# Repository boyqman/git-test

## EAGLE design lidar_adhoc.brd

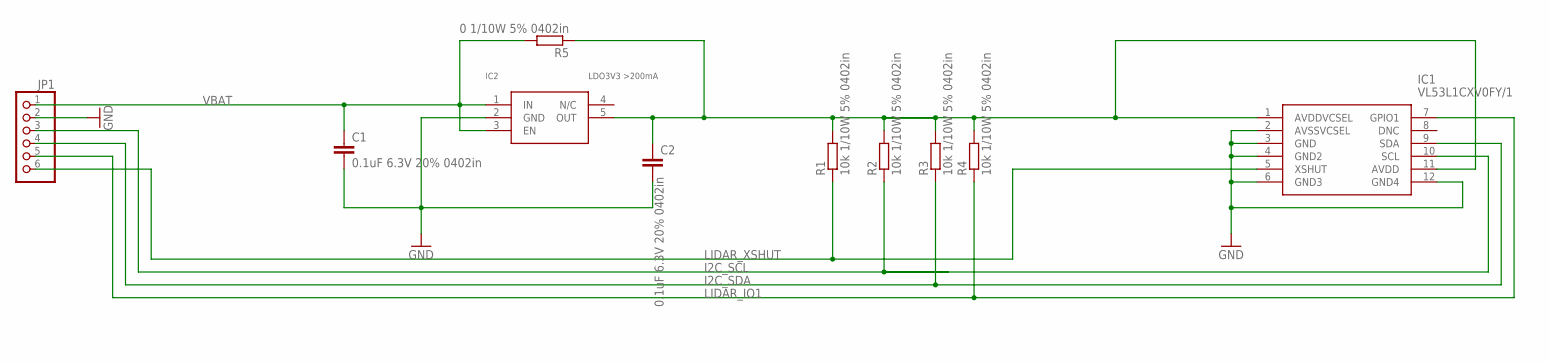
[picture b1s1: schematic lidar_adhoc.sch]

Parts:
C1, C2: 0.1uF 6.3V 20% 0402in; C0402K
IC1: VL53L1CXV0FY/1; VL53L1CXV0FY1
IC2: LDO3V3 >200mA; LDO3V3
JP1: PINHD-1X6; 1X06
R1, R2, R3, R4: 10k 1/10W 5% 0402in; C0402K
R5: 0 1/10W 5% 0402in; C0402K

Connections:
3V3_LIDAR1: C2.1, IC1.1 (AVDDVCSEL), IC1.11 (AVDD), IC2.5 (OUT), R1.2, R2.2, R3.2, R4.2, R5.1
GND: C1.2, C2.2, IC1.2 (AVSSVCSEL), IC1.3 (GND), IC1.4 (GND2), IC1.6 (GND3), IC1.12 (GND4), IC2.2 (GND), JP1.2
I2C_SCL: IC1.10 (SCL), JP1.3, R2.1
I2C_SDA: IC1.9 (SDA), JP1.4, R3.1
LIDAR_IO1: IC1.7 (GPIO1), JP1.5, R4.1
LIDAR_XSHUT: IC1.5 (XSHUT), JP1.6, R1.1
VBAT: C1.1, IC2.1 (IN), IC2.3 (EN), JP1.1, R5.2

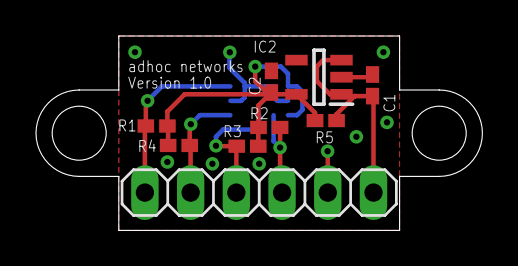
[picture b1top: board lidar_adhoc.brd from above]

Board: 2 copper layers, 24.8 x 10.8 mm, 10 parts (1 on the bottom side), 7 nets.

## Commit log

2022-10-18 add file
2023-03-07 add text01
2023-03-07 add lna
2023-03-07 add lna02
2023-09-24 add file test ocr for rasp
